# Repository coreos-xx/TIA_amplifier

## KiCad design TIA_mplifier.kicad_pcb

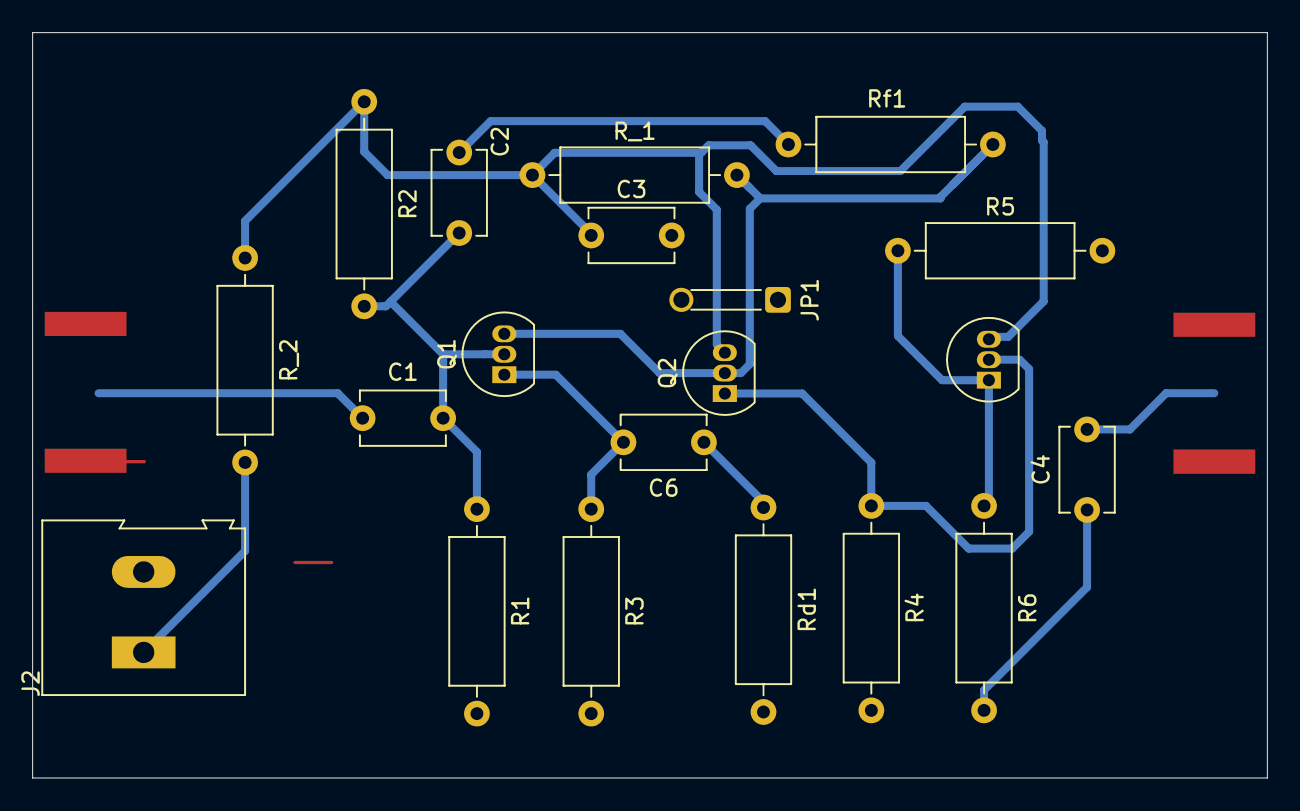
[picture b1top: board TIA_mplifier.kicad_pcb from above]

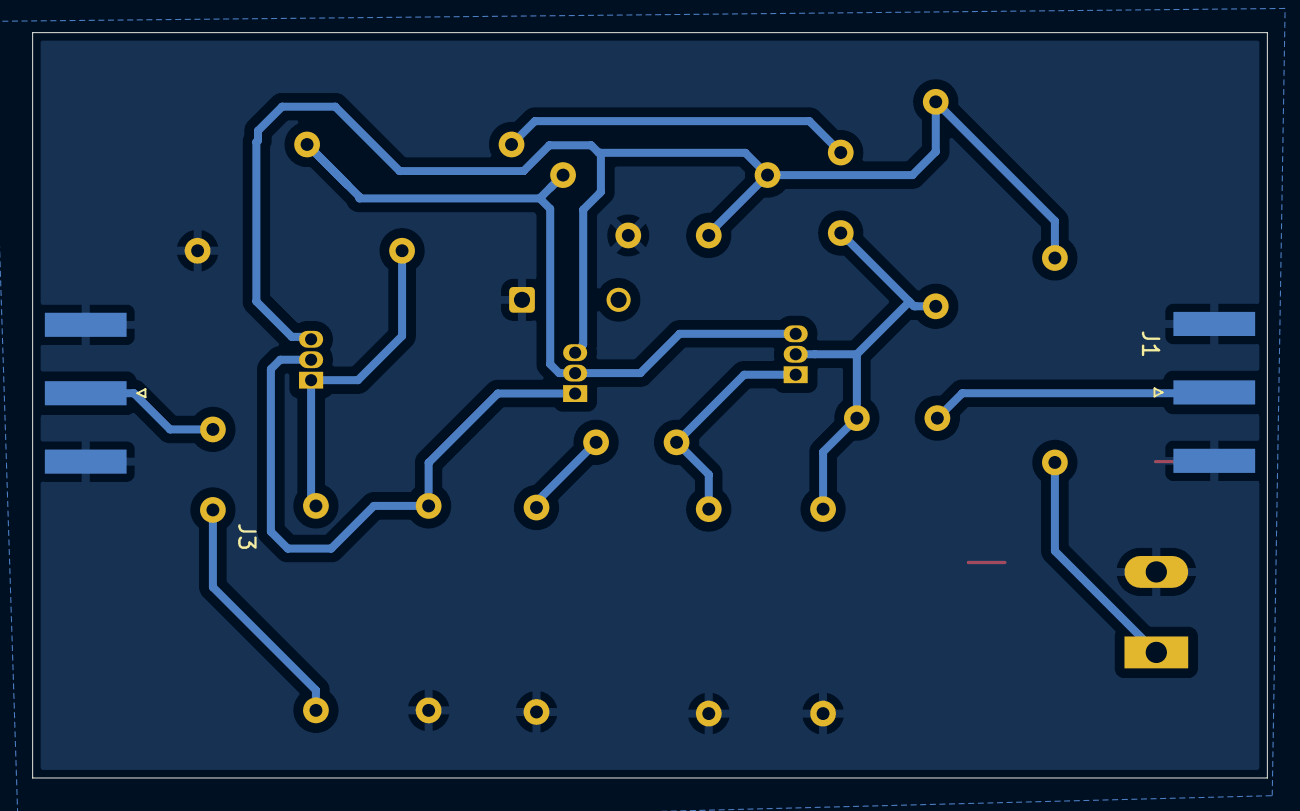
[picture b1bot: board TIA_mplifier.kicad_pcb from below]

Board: 2 copper layers, 76.7 x 46.3 mm, 22 parts (2 on the bottom side), 13 nets.

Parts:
C1, C2, C3, C4, C6: 100nF; C_Disc_D5.1mm_W3.2mm_P5.00mm
J1: RF_in; SMA_Amphenol_132289_EdgeMount
J2: Screw_Terminal_01x02; TerminalBlock_Altech_AK300-2_P5.00mm
J3: RF_out; SMA_Amphenol_132289_EdgeMount
JP1: Jumper_2_Bridged; SolderWire-0.1sqmm_1x01_D0.4mm_OD1mm_Relief
Q1, Q2, Q3: 2N3904; TO-92_Inline
R1, R4: 2.2k; R_Axial_DIN0309_L9.0mm_D3.2mm_P12.70mm_Horizontal
R2: 10k; R_Axial_DIN0309_L9.0mm_D3.2mm_P12.70mm_Horizontal
R3: 180; R_Axial_DIN0309_L9.0mm_D3.2mm_P12.70mm_Horizontal
R5: 470; R_Axial_DIN0309_L9.0mm_D3.2mm_P12.70mm_Horizontal
R6: 47; R_Axial_DIN0309_L9.0mm_D3.2mm_P12.70mm_Horizontal
R_1: 330; R_Axial_DIN0309_L9.0mm_D3.2mm_P12.70mm_Horizontal
R_2: 10; R_Axial_DIN0309_L9.0mm_D3.2mm_P12.70mm_Horizontal
Rd1: 4.7; R_Axial_DIN0309_L9.0mm_D3.2mm_P12.70mm_Horizontal
Rf1: 1800; R_Axial_DIN0309_L9.0mm_D3.2mm_P12.70mm_Horizontal

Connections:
GND: C3.2, J1.2 (Ext), J2.2, J3.2 (Ext), JP1.1 (A), R1.2, R3.2, R4.2, R5.2, Rd1.2
unnamed: C2.1, Rf1.1
unnamed: C4.1, R6.2
unnamed: C6.1, Rd1.1
unnamed: C1.1, J1.1 (In)
unnamed: J2.1, R_2.2
unnamed: C4.2, J3.1 (In)
unnamed: C1.2, C2.2, Q1.2 (B), R1.1, R2.2
unnamed: Q1.3 (C), Q2.2 (B), R_1.2, Rf1.2
unnamed: C6.2, Q1.1 (E), R3.1
unnamed: C3.1, Q2.3 (C), Q3.3 (C), R2.1, R_1.1, R_2.1
unnamed: Q2.1 (E), Q3.2 (B), R4.1
unnamed: Q3.1 (E), R5.1, R6.1

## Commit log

2025-03-26 added production zip file
